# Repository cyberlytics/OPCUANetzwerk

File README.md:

# opcua_netzwerk

## Getting started

To make it easy for you to get started with GitLab, here's a list of recommended next steps.

Already a pro? Just edit this README.md and make it your own. Want to make it easy? [Use the template at the bottom](#editing-this-readme)!

## Add your files

- [ ] [Create](https://docs.gitlab.com/ee/user/project/repository/web_editor.html#create-a-file) or [upload](https://docs.gitlab.com/ee/user/project/repository/web_editor.html#upload-a-file) files
- [ ] [Add files using the command line](https://docs.gitlab.com/ee/gitlab-basics/add-file.html#add-a-file-using-the-command-line) or push an existing Git repository with the following command:

```
cd existing_repo
git remote add origin https://git.oth-aw.de/opcua_team/opcua_netzwerk.git
git branch -M main
git push -uf origin main
```

## Integrate with your tools

- [ ] [Set up project integrations](https://git.oth-aw.de/opcua_team/opcua_netzwerk/-/settings/integrations)

## Collaborate with your team

- [ ] [Invite team members and collaborators](https://docs.gitlab.com/ee/user/project/members/)
- [ ] [Create a new merge request](https://docs.gitlab.com/ee/user/project/merge_requests/creating_merge_requests.html)
- [ ] [Automatically close issues from merge requests](https://docs.gitlab.com/ee/user/project/issues/managing_issues.html#closing-issues-automatically)
- [ ] [Enable merge request approvals](https://docs.gitlab.com/ee/user/project/merge_requests/approvals/)
- [ ] [Automatically merge when pipeline succeeds](https://docs.gitlab.com/ee/user/project/merge_requests/merge_when_pipeline_succeeds.html)

## Test and Deploy

Use the built-in continuous integration in GitLab.

- [ ] [Get started with GitLab CI/CD](https://docs.gitlab.com/ee/ci/quick_start/index.html)
- [ ] [Analyze your code for known vulnerabilities with Static Application Security Testing(SAST)](https://docs.gitlab.com/ee/user/application_security/sast/)
- [ ] [Deploy to Kubernetes, Amazon EC2, or Amazon ECS using Auto Deploy](https://docs.gitlab.com/ee/topics/autodevops/requirements.html)
- [ ] [Use pull-based deployments for improved Kubernetes management](https://docs.gitlab.com/ee/user/clusters/agent/)
- [ ] [Set up protected environments](https://docs.gitlab.com/ee/ci/environments/protected_environments.html)

***

# Editing this README

When you're ready to make this README your own, just edit this file and use the handy template below (or feel free to structure it however you want - this is just a starting point!). Thank you to [makeareadme.com](https://www.makeareadme.com/) for this template.

## Suggestions for a good README
Every project is different, so consider which of these sections apply to yours. The sections used in the template are suggestions for most open source projects. Also keep in mind that while a README can be too long and detailed, too long is better than too short. If you think your README is too long, consider utilizing another form of documentation rather than cutting out information.

## Name
Choose a self-explaining name for your project.

## Description
Let people know what your project can do specifically. Provide context and add a link to any reference visitors might be unfamiliar with. A list of Features or a Background subsection can also be added here. If there are alternatives to your project, this is a good place to list differentiating factors.

## Badges
On some READMEs, you may see small images that convey metadata, such as whether or not all the tests are passing for the project. You can use Shields to add some to your README. Many services also have instructions for adding a badge.

## Visuals
Depending on what you are making, it can be a good idea to include screenshots or even a video (you'll frequently see GIFs rather than actual videos). Tools like ttygif can help, but check out Asciinema for a more sophisticated method.

## Installation
Within a particular ecosystem, there may be a common way of installing things, such as using Yarn, NuGet, or Homebrew. However, consider the possibility that whoever is reading your README is a novice and would like more guidance. Listing specific steps helps remove ambiguity and gets people to using your project as quickly as possible. If it only runs in a specific context like a particular programming language version or operating system or has dependencies that have to be installed manually, also add a Requirements subsection.

## Usage
Use examples liberally, and show the expected output if you can. It's helpful to have inline the smallest example of usage that you can demonstrate, while providing links to more sophisticated examples if they are too long to reasonably include in the README.

## Support
Tell people where they can go to for help. It can be any combination of an issue tracker, a chat room, an email address, etc.

## Roadmap
If you have ideas for releases in the future, it is a good idea to list them in the README.

## Contributing
State if you are open to contributions and what your requirements are for accepting them.

For people who want to make changes to your project, it's helpful to have some documentation on how to get started. Perhaps there is a script that they should run or some environment variables that they need to set. Make these steps explicit. These instructions could also be useful to your future self.

You can also document commands to lint the code or run tests. These steps help to ensure high code quality and reduce the likelihood that the changes inadvertently break something. Having instructions for running tests is especially helpful if it requires external setup, such as starting a Selenium server for testing in a browser.

## Authors and acknowledgment
Show your appreciation to those who have contributed to the project.

## License
For open source projects, say how it is licensed.

## Project status
If you have run out of energy or time for your project, put a note at the top of the README saying that development has slowed down or stopped completely. Someone may choose to fork your project or volunteer to step in as a maintainer or owner, allowing your project to keep going. You can also make an explicit request for maintainers.

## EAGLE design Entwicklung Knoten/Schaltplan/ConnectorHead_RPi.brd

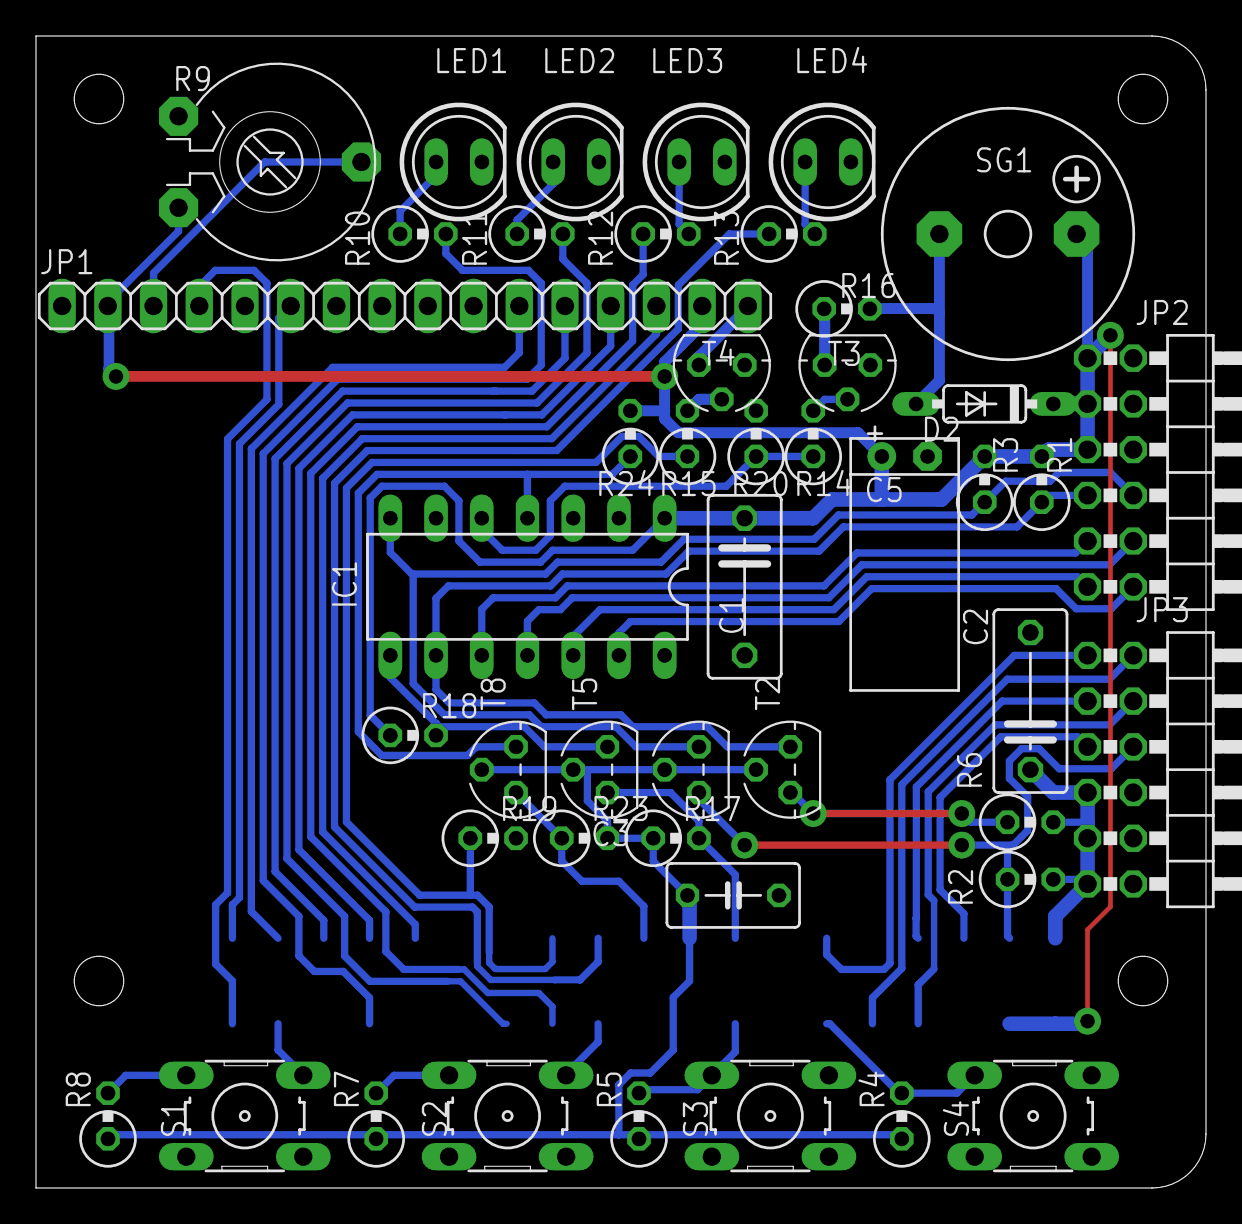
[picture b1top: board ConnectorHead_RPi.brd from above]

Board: 2 copper layers, 65.0 x 64.0 mm, 47 parts (1 on the bottom side), 47 nets.

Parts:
C1, C2: 330nF/100V; C075-042X103
C3: 330nF/63V; C050-035X075
C5: 100uF/16V; E2,5-6_FLAT_DOWN
D2: 1N4148DO35-7; DO35-7
IC1: TINY24/44/84-PU; DIL14
JP1: Display; 1X16F
JP2: Connector 5V; 2X06/90
JP3: Connector 3.3V; 2X06/90
LED1: Blue; LED5MM
LED2: Red; LED5MM
LED3: Orange; LED5MM
LED4: Green; LED5MM
R1, R2, R3, R6, R17, R18, R19, R20, R23, R24: 10k; 0309V
R4, R5, R7, R8: 1k; 0309V
R9: 10k; PT-10
R10, R11, R12, R13, R14, R15: 220R; 0309V
R16: 10R; 0309V
S1: Button_1; B3F-10XX
S2: Button_2; B3F-10XX
S3: Button_3; B3F-10XX
S4: Button_4; B3F-10XX
SG1: F/CM12P
T1, T2, T3, T4, T5, T8: 2N7000; TO92
U$1: 2X20

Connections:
+3V3: C2.1, C3.1, JP3.7, JP3.9, JP3.11, R2.2, R4.1, R5.1, R6.2, R7.1, R8.1, R17.1, R23.2, T1.2, T2.2, T5.2, T8.2, U$1.1, U$1.17
+5V: C1.1, C5.+, D2.C, IC1.1, JP1.2, JP1.15, JP2.1, JP2.3, JP2.5, R1.2, R3.2, R9.2, R18.1, R24.2, SG1.+, U$1.2, U$1.4
DSP_BL: R15.1, R19.1, U$1.23
DSP_BL_GND: JP1.16, T4.1
DSP_CONTRAST: JP1.3, R9.3
DSP_D4: JP1.11, U$1.35
DSP_D5: JP1.12, U$1.33
DSP_D6: JP1.13, U$1.31
DSP_D7: JP1.14, U$1.29
DSP_EN: JP1.6, U$1.37
DSP_REGSEL: JP1.4, U$1.38
GND: C1.2, C2.2, C3.2, C5.-, IC1.14, JP1.1, JP1.5, JP2.2, JP2.4, JP2.6, JP3.8, JP3.10, JP3.12, LED1.K, LED2.K, LED3.K, LED4.K, R9.1, R19.2, R20.2, S1.1, S1.2, S2.1, S2.2, S3.1, S3.2, S4.1, S4.2, T3.3, T4.3, U$1.6, U$1.9, U$1.14, U$1.20, U$1.25, U$1.30, U$1.34, U$1.39
GPIO0_3V3: JP3.1, U$1.11
GPIO0_5V: IC1.10, JP2.9
GPIO1_3V3: JP3.2, U$1.10
GPIO1_5V: IC1.11, JP2.10
GPIO2_3V3: JP3.3, U$1.7
GPIO2_5V: IC1.12, JP2.11
GPIO3_3V3: JP3.4, U$1.8
GPIO3_5V: IC1.13, JP2.12
I2C_SCL_3V3: JP3.5, R6.1, T2.3, U$1.5
I2C_SCL_5V: IC1.9, JP2.7, R1.1, T2.1
I2C_SDA_3V3: JP3.6, R2.1, T1.3, U$1.3
I2C_SDA_5V: IC1.7, JP2.8, R3.1, T1.1
LED_B: R10.2, U$1.32
LED_G: R13.1, U$1.21
LED_O: R12.1, U$1.24
LED_R: R11.2, U$1.26
unnamed: LED1.A, R10.1
unnamed: LED2.A, R11.1
unnamed: LED3.A, R12.2
unnamed: LED4.A, R13.2
unnamed: R16.1, T3.1
unnamed: D2.A, R16.2, SG1.-
unnamed: R14.2, T3.2
unnamed: R8.2, S1.4
unnamed: R15.2, T4.2
unnamed: R7.2, S2.4
SIG_B1: S1.3, U$1.36
SIG_B2: S2.3, U$1.22
SIG_B3: R5.2, S3.4, U$1.16
SIG_B4: R4.2, S4.4, U$1.12
SOUND_SIG: IC1.5, R14.1, R20.1
UC_PROG_3V3: R17.2, T5.3, U$1.15
UC_PROG_5V: IC1.8, R18.2, T5.1
UC_RESET_3V3: R23.1, T8.3, U$1.19
UC_RESET_5V: IC1.4, R24.1, T8.1

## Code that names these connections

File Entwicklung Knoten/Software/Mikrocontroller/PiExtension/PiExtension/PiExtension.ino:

/**
 * @project		: OPCUA Sensor Netzwerk im Fach "Web Semantic Technology" Wintersemester 2022/23 Team Gruen
 * @file		: PIExtension.ino
 * @description	:
 *		Implementiert das Hauptprogramm des Mikrocontrollers auf der Erweiterungsplatine für einen Sensorknoten.
 *		Steuert die GPIOs des 5V Sensor-Interfaces. Implementiert verschiedene Funktionen zum Ansteuern/Auslesen
 *		von Sensoren/Aktoren.
 *
 * @author		: Manuel Zimmermann <m.zimmermann1@oth-aw.de>
 * @date		: 2022-12-06 07:10:12
 * @version		: 1.0
 */

#include <Arduino.h>
#include "ATTINY_x4_Register.h"
#include "SLTask.h"
#include "IICSlave.h"
#include "IIICCallable.h"
#include "ADCPin.h"
#include "PWM8Pin.h"



//#define OSC_CALIBRATION		112	//NODE 1
//#define OSC_CALIBRATION		132	//NODE 2
//#define OSC_CALIBRATION		128	//NODE 3
#define IIC_ADDRESS			100
#define N_GPIOS				5



ERROR_t iic_heartbeat(IICRequest* req, IICResponse* rsp);
ERROR_t iic_received(IICRequest* req, IICResponse* rsp);
int main();

ADCPin	gpio0(HW::port_a, 3); //GPIO0_5V
ADCPin	gpio1(HW::port_a, 2); //GPIO1_5V
ADCPin	gpio2(HW::port_a, 1); //GPIO2_5V
ADCPin	gpio3(HW::port_a, 0); //GPIO3_5V
PWM8Pin gpio4(HW::port_b, 2); //Sound Signal

IIICCallable* gpios[N_GPIOS]{ &gpio0, &gpio1, &gpio2, &gpio3, &gpio4 };


//Schreibt alle empfangenen Bytes wieder zurück
ERROR_t iic_heartbeat(IICRequest* req, IICResponse* rsp) {
	uint8_t len = req->size();
	for (uint8_t i = 0; i < len; i++) {
		ERROR_t e;
		byte b;
		
		if ((e = req->read(b))  != ERROR_t::GENERAL_OK) return e;
		if ((e = rsp->write(b)) != ERROR_t::GENERAL_OK) return e;
	}

	return ERROR_t::GENERAL_OK;
}

ERROR_t iic_received(IICRequest* req, IICResponse* rsp) {
	ERROR_t e;

	//Erstes Byte entspricht cmd
	uint8_t cmd;
	if ((e = req->read(cmd)) != ERROR_t::GENERAL_OK) return e;
	if (cmd == Function::HEARTBEAT) return iic_heartbeat(req, rsp); //Heartbeat? -> Eingabepuffer 1:1 wieder zurückschreiben

	///Ab hier entspricht 2tes Byte der GPIO-Pinnummer
	uint8_t gpioNr;
	if ((e = req->read(gpioNr)) != ERROR_t::GENERAL_OK) return e;
	if (gpioNr >= N_GPIOS) return ERROR_t::GPIO_NOT_EXISTING;
	return gpios[gpioNr]->call((Function)cmd, req, rsp); //GPIO ansprechen
}

int main() {
	//INIT 
	HW::sys->osccal = OSC_CALIBRATION;
	IIC.begin(IIC_ADDRESS, iic_received);
	
	sei();
	
	//LOOP
	for (;;) {
		SLTask::proceedTasks();
	}
	
	return 0;
}

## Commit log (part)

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2022-11-08 Konzeptpapier Anmerkungen MZ
2022-11-12 Added text for section "Sensoren + Kommunikation"
2022-11-15 Added new architecture graphic and created new pdf
2022-11-25 Added basic information model and test server
2022-11-26 Setup backend structure
2022-11-26 git config test
    Former-commit-id: 0a45321a0faa428a1961ebfa531ae46f0511c59b
2022-11-26 Added KeyPass Database
    Former-commit-id: 137d0690a105542459f7d1ce8308ac88659fd6a0
2022-11-26 Passwort Ordner in Security umbenannt
2022-11-26 Added password for opcuaclient
    Former-commit-id: f3f4761612a2e7acd129f609679fd0462f116188
2022-11-26 Updated information model
    Former-commit-id: d3db4ccf09c93a3e7d72d6ec525f38c6b4983f91
2022-11-26 Updated Example Server. Sensor Values get updated with dummy data
2022-11-26 ngx admin template, without examples [REQUIRES node version 14.15.0]
    the ngx admin template
    removed all example pages
    the entire raw template is available in the .zip file
    WARNING: node version 14.15.0 required
    use the Node Version Manager to downgrade your node version:
    https://github.com/nvm-sh/nvm
2022-11-28 Anpassung der VPN Zugangskonten für die Knoten (ACHTUNG! Passwörter haben sich geändert!) - Feste Vergabe von IPs auch an die Knoten - Einrichtung eigener Domänen für Server/Nodes - Server: server.sn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
2022-11-29 VPN Security improved
    Former-commit-id: f01691be7268ffa26e09296048fba9c00bd2b814
2022-11-29 Security improved
2022-11-29 Git Cleanup
    Former-commit-id: ae5dc69ff3cb9fd38e1fb5248f5416d153d90342
2022-12-01 Default Git Ignore für Visual Studio + Eagle PCB
    Former-commit-id: f395e5c6a15dd4674316e520b02f119540b7232c
2022-12-01 Eagle Schaltplan erstellt (noch nicht validiert!)
    Former-commit-id: b32482e994105c5fc459f959e4ad489d75ffd700
2022-12-02 Installationsscript überarbeitet Client-Installationsscript mit Funktion zum Flashen des Mikrocontrollers ergänzt
    Former-commit-id: d146af5d701516e11ea34776beaa514836b797c6
2022-12-02 - Installationsscript überarbeitet - Client-Installationsscript mit Funktion zum Flashen des Mikrocontrollers ergänzt
2022-12-03 Setup backend structure
    Former-commit-id: 07d1aca74be71a971b1998a3b97838c5a5ded302
2022-12-03 git config test
    Former-commit-id: f496258fe5a99c7f353b1d8731dfe546f797820e
2022-12-03 created sensorDto
2022-12-03 Module for Sensornode and simple linechart component
    line chart component is only for testing for now -> not final/finshed
2022-12-04 added new backend functionalities
    Former-commit-id: aa97d8370e6c2f96a46c9ff5dd3db32e4e3888c3
2022-12-04 Finished LineChartComponent
    Added moments package -> run 'npm i' again!
    Former-commit-id: 24c053c382353d92778baa25900d745896be76e8
2022-12-05 TemperatureGauge1.1
2022-12-05 Removed Husky
    Former-commit-id: 4a381a570b9eb404d4390a46c3d563cb3229d780
2022-12-05 Gauge Styleing
2022-12-06 Change date from string to datetime-object
2022-12-06 Add route for getting filtered values
    Former-commit-id: fb5d050fabc642b8473ecbfbf767c4c49a9ba1ba
2022-12-06 added technical Report and .gitignore
    Former-commit-id: fd5b6fd5efd05c0a9a6cfd9da89b11b5f3f9823d
2022-12-06 small technical report adjustments
2022-12-06 Added Flip Card Component
2022-12-06 Changed gauge component data input
    Former-commit-id: 7194a41556a6b85ec2ee42bc8b7e65e20e854870
2022-12-06 linechart log -> normal
2022-12-07 adjustments in technical report
    Former-commit-id: 5eaaaa325bfe05c7c25a959b099812a8fb2667be
2022-12-07 Platinen Routing erstellt
    Former-commit-id: 2a54272727757d3238e7998732707be59b908f07
2022-12-07 CAM Files zum Fräsen der Platine erstellt
    Former-commit-id: 2b0b3d39396eb5e4295dae6a983a3e444d2ebde6
2022-12-07 Grundlegendes 3D Modell erstellt
    Former-commit-id: 83a7c192f599a2c81ed5c942e02c3e17ca674f32
2022-12-12 Gantt 2.0
    Neues Gantt Model wird ausprobiert aber echarts.graphic ist undefiniert (aus längere Recherche könnte es sein, dass diese Funktionalität in Typescript nicht unterstützt wird) --> eventuelle Lösung: c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
2022-12-13 changed camel-case to snake-case
    Former-commit-id: e8b2f65c0aef6378b68150c57c54e545bcd71274
2022-12-13 Started implementig data from backend
2022-12-14 Platinen CAM Dateien + Fräsdateien erstellt
    Former-commit-id: 2424ae5df393cf0547cad5ff5208894c3e429b06
2022-12-14 Software für Mikrocontroller - Implementierung I2C begonnen
    Former-commit-id: 8721088b8102f5fc9ac2e90d412f662e97146d48
2022-12-14 VPN Installationsscript angepasst, sodass DNS Server vom VPN genutzt wird
    Former-commit-id: eda79a51d845afed79dca1266602b81d0877a0a1
2022-12-14 DNS Service im VPN Installationsscript angepasst
2022-12-14 Update for manually setting ntp
2022-12-14 Gantt2.1
    Former-commit-id: 0d64559595bdd3f1e41203e527859f37bf7de9e5
2022-12-14 Navigator now only shows real sensornodes
2022-12-14 Datepicker in header, not working yet
2022-12-15 Made Datepicker Functional
2022-12-15 diverses
2022-12-15 Fixed Linechart datapoint order
2022-12-15 Datenblätter zu Sensoren / Hardware ergänzt
    Former-commit-id: a4e524c1222b556a172b9e9ef0f5d45694b35bbb
2022-12-15 - RPC Schnittstelle für IOPin und ADCPin implementiert - Python Bibliothek als RPC Wrapper implementiert - Tests für I²C Kommunikation implementiert - Tests für IOPin und ADCPin implementiert - klein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
2022-12-15 Mikrocontroller Firmware kompiliert
    Former-commit-id: 956a03e1b34e660706bdd419c92c6a34dd47451a
2022-12-15 Installationsscript mit Grundeinrichtungsfunktion erstellt
    Former-commit-id: 5d812895f3c74c11f82a096a51efd5758661b5c6
2022-12-17 Add structure for actuators
    Former-commit-id: 040cb3170b81ec3a611915733b4700ca0abb3567
2022-12-18 Subclassed all actuators and make them controllable trough an api request
    Former-commit-id: b6e207a9a6362966d98f199e2f95e4e55b4aec90
2022-12-18 Add response model to routes where it missed
2022-12-19 Mikrocontroller Software angepasst
    IIC wird nun über Interrupts gesteuert, da Start Condition bei zu großer Verzögerung nicht richtig erkannt wurde.
    IIC Callbacks werden nun ebenfalls in der ISR ausgeführt
    Former-commit-id: a17ebc50960c24b5026d6109b0a02ca3154fe676
2022-12-19 Namenslabel auf Platine für bessere Leserlichkeit neu positioniert
2022-12-19 Added Server and Client scripts for OPCUA
2022-12-19 added timeout to wait for vpn
2022-12-19 Cleanup for main merge
    Former-commit-id: 1fdd7d88157c05a2d8883fbf9626654d53f40730
2022-12-20 changed presence sensor
2022-12-20 add value in presence sensor
    Former-commit-id: 6bf83186b1bbc30e5c0bc7153956614f00d28a5f
2022-12-20 Softwareerweiterung Mikrocontroller
    - PWM Funktion auf Mikrocontroller implementiert (unvollständig)
    - PWM Funktion in Lib implementiert
    - Kleinere Bugfixes im Code des Mikrocontroller
    - Tests für PWM implementiert
    - Tests für Protokoll implementiert
    - Refactoring Lib
2022-12-21 updated tech report
    Former-commit-id: 1959689180c76bde4f31f66a22cbee45ab63b93c
2022-12-21 Firmmware Build erstellt
2022-12-21 Added LCD Input Component
2022-12-22 AirPresure Table Changes and styleing
    Former-commit-id: e140509cb344eaca2df3d8d304676cafa2f8c8d4
2022-12-22 Finished AirQuality Component
    Former-commit-id: c31286a455e364d6245a649ce219a298f783577a
2022-12-22 Added default timespan to datepicker
2022-12-22 Fixed Datepickers
2022-12-22 Gauge Verbesserung
    Former-commit-id: 2accf51ea8f339e1d5b5054ffeca3711a91286a7
2022-12-22 Added menu functionality to lcd display
    Former-commit-id: 2b5f263af1bef71f5cb4fb181504a13c350f96c5
2022-12-22 add /sensornodes route
2022-12-22 Bug found and fixed O:)
    Former-commit-id: c74ca95b82a2ec34af9629e64a77da5364582673
2022-12-22 Firmware Build erstellt
    Former-commit-id: 47a7e319f4f4ae5d710561084c5a0c4abfbfff80
2022-12-22 Added toggle to view Live Data
2022-12-23 Update Client: - Now blue LED should update according to connection status_led_thread - Other LEDS are now used for measurement
2022-12-23 Gantt & DashboardService
    Gantt funktioniert mit testdaten,
    Dashboard Service erstellt (Funktionen)
2022-12-23 Changed Air presure unit to bar for easy reading
    Former-commit-id: b6066ddfe53fac5ef56f5956a6b815af235dd896
2022-12-23 LCD Input now gets the current value displayed on the lcd
    Former-commit-id: 08bfad70178c32730bd53c13267c2eec4a8ae8dd
2022-12-23 Rearaged Dashboard and added http error handeling with toast
2022-12-23 Added Test to lineChart
2022-12-26 bisschen was für frontend geschrieben (hat noch verbesserungsbedarf & test abdeckung und services fehlen)
    Former-commit-id: 66f1bed3cc6a6201d6e93b86f5de68e4232da8d6
2022-12-26 Add new directory
    Former-commit-id: 403314645ca550e7edeb5672a8d8e958b8b7f76a
2022-12-27 Added music functionality and templated strings
2022-12-27 Added some Tests
    für dashboardservice und Gantt
    Former-commit-id: 4a5be14ac9656c66dd2bbf2e6e4d2ba937f34cf5
2022-12-29 Refactoring of main script
    Former-commit-id: a3b4b8d0f5c4ab1a873c6534511379031b68dcb5
2023-01-02 Gantt Überlappung gefixed + verbessert
    Former-commit-id: 1fb4eeb1da808d4aee6348246749b1526cccb253
2023-01-04 3D Gehäuse für Sensorknoten erstellt (Unvollständig)
2023-01-04 Fixed Gauges not rounding numbers, when switching Theme
    Former-commit-id: 0d3ec44ecc72e0bf6131806d1b34eab3856e0fd2
2023-01-04 added component to set Frequency of buzzer
    Former-commit-id: 6c18913031b1e31eba83c277510abbbf6964b7ed
2023-01-04 Added gitignore
    Former-commit-id: 7dd82f4c8f5d77de20a8ff5bafee6060627a56ad
2023-01-04 Added Led-Display component to header
    Former-commit-id: 4fbcd8b4bed46233c7641a4ffde19697bc27baa1
2023-01-04 Added section for opcua semantics and added text for sensors-part
    Former-commit-id: 49bec74602ad086d26694df65a2bcd8dbe6d3ba2
2023-01-04 Fixed copy/paste error in sensor section
    Former-commit-id: b929a521c0481a8afaf0d577e104a502956675ce
2023-01-04 Removed mock data services
2023-01-04 Removed example dashboard compnent and module
    Former-commit-id: 547d48ee7982a7f6babc9a2a16624b22c6e11cbc
2023-01-04 Removed example data services
    Former-commit-id: e7dc34fb1c759f18d9991e4cd7175c7667814b92
2023-01-04 Fixed Bug where current Values for LCD display wont show
2023-01-04 Fixed a bug where the current frequency of the piezo element wont show in the input
2023-01-05 - Small bugfix on lcd_display.py - Re-Added music functionality to menu
2023-01-05 Added string parsing for boolean values in the led display
2023-01-05 removed console.log spam
    Former-commit-id: 9c7ffed6ecfab486931a3598748315111293c883
2023-01-05 added function to shorten large datasets (average of 10) (not used)
    Former-commit-id: 66cf7f21d4c102c6144bed20c278411bbc1d78a2
2023-01-08 Update gitinspector
    Former-commit-id: c4e2588111d50c62cbdead7e58f07f45067d4f4a
2023-01-08 tech report improvements
2023-01-08 Update Frontend Complete
    Former-commit-id: c27d9b3bd0469f8af40f86d7039392a7e0b71771
2023-01-09 dynamic backend endpoint
2023-01-09 Changed tab title
2023-01-09 fixed styling linechart component
    Former-commit-id: 3848541f5605fa6f62cad2fe51b61821d4b428b3
2023-01-09 enabled production mode
    Former-commit-id: 1f15594ecd8e5ee8b1173dfb9593be97ae14c24c
2023-01-09 removed function
    Former-commit-id: 027e8889ef2fcb0bdb6850ca529024be4dd17a38
2023-01-09 removed forgotten import
    Former-commit-id: 355359f16e743f9a74a8944810404c64087ec58e
2023-01-10 fixup
2023-01-10 updated technical report
2023-01-10 maybe final version of tech report
2023-01-10 tech report
2023-01-15 3D Modell gefertigt
    Former-commit-id: 048caa6871024230bb87c9b5f8b344531e8a2806
2023-01-15 Mikrocontroller Oszillatoren kalibriert + Firmware für jeden Knoten erstellt
2023-01-16 Small bugfix for client
    Former-commit-id: 23dde4735ce04a8ec4a46a1324e8f6677c7caf97
